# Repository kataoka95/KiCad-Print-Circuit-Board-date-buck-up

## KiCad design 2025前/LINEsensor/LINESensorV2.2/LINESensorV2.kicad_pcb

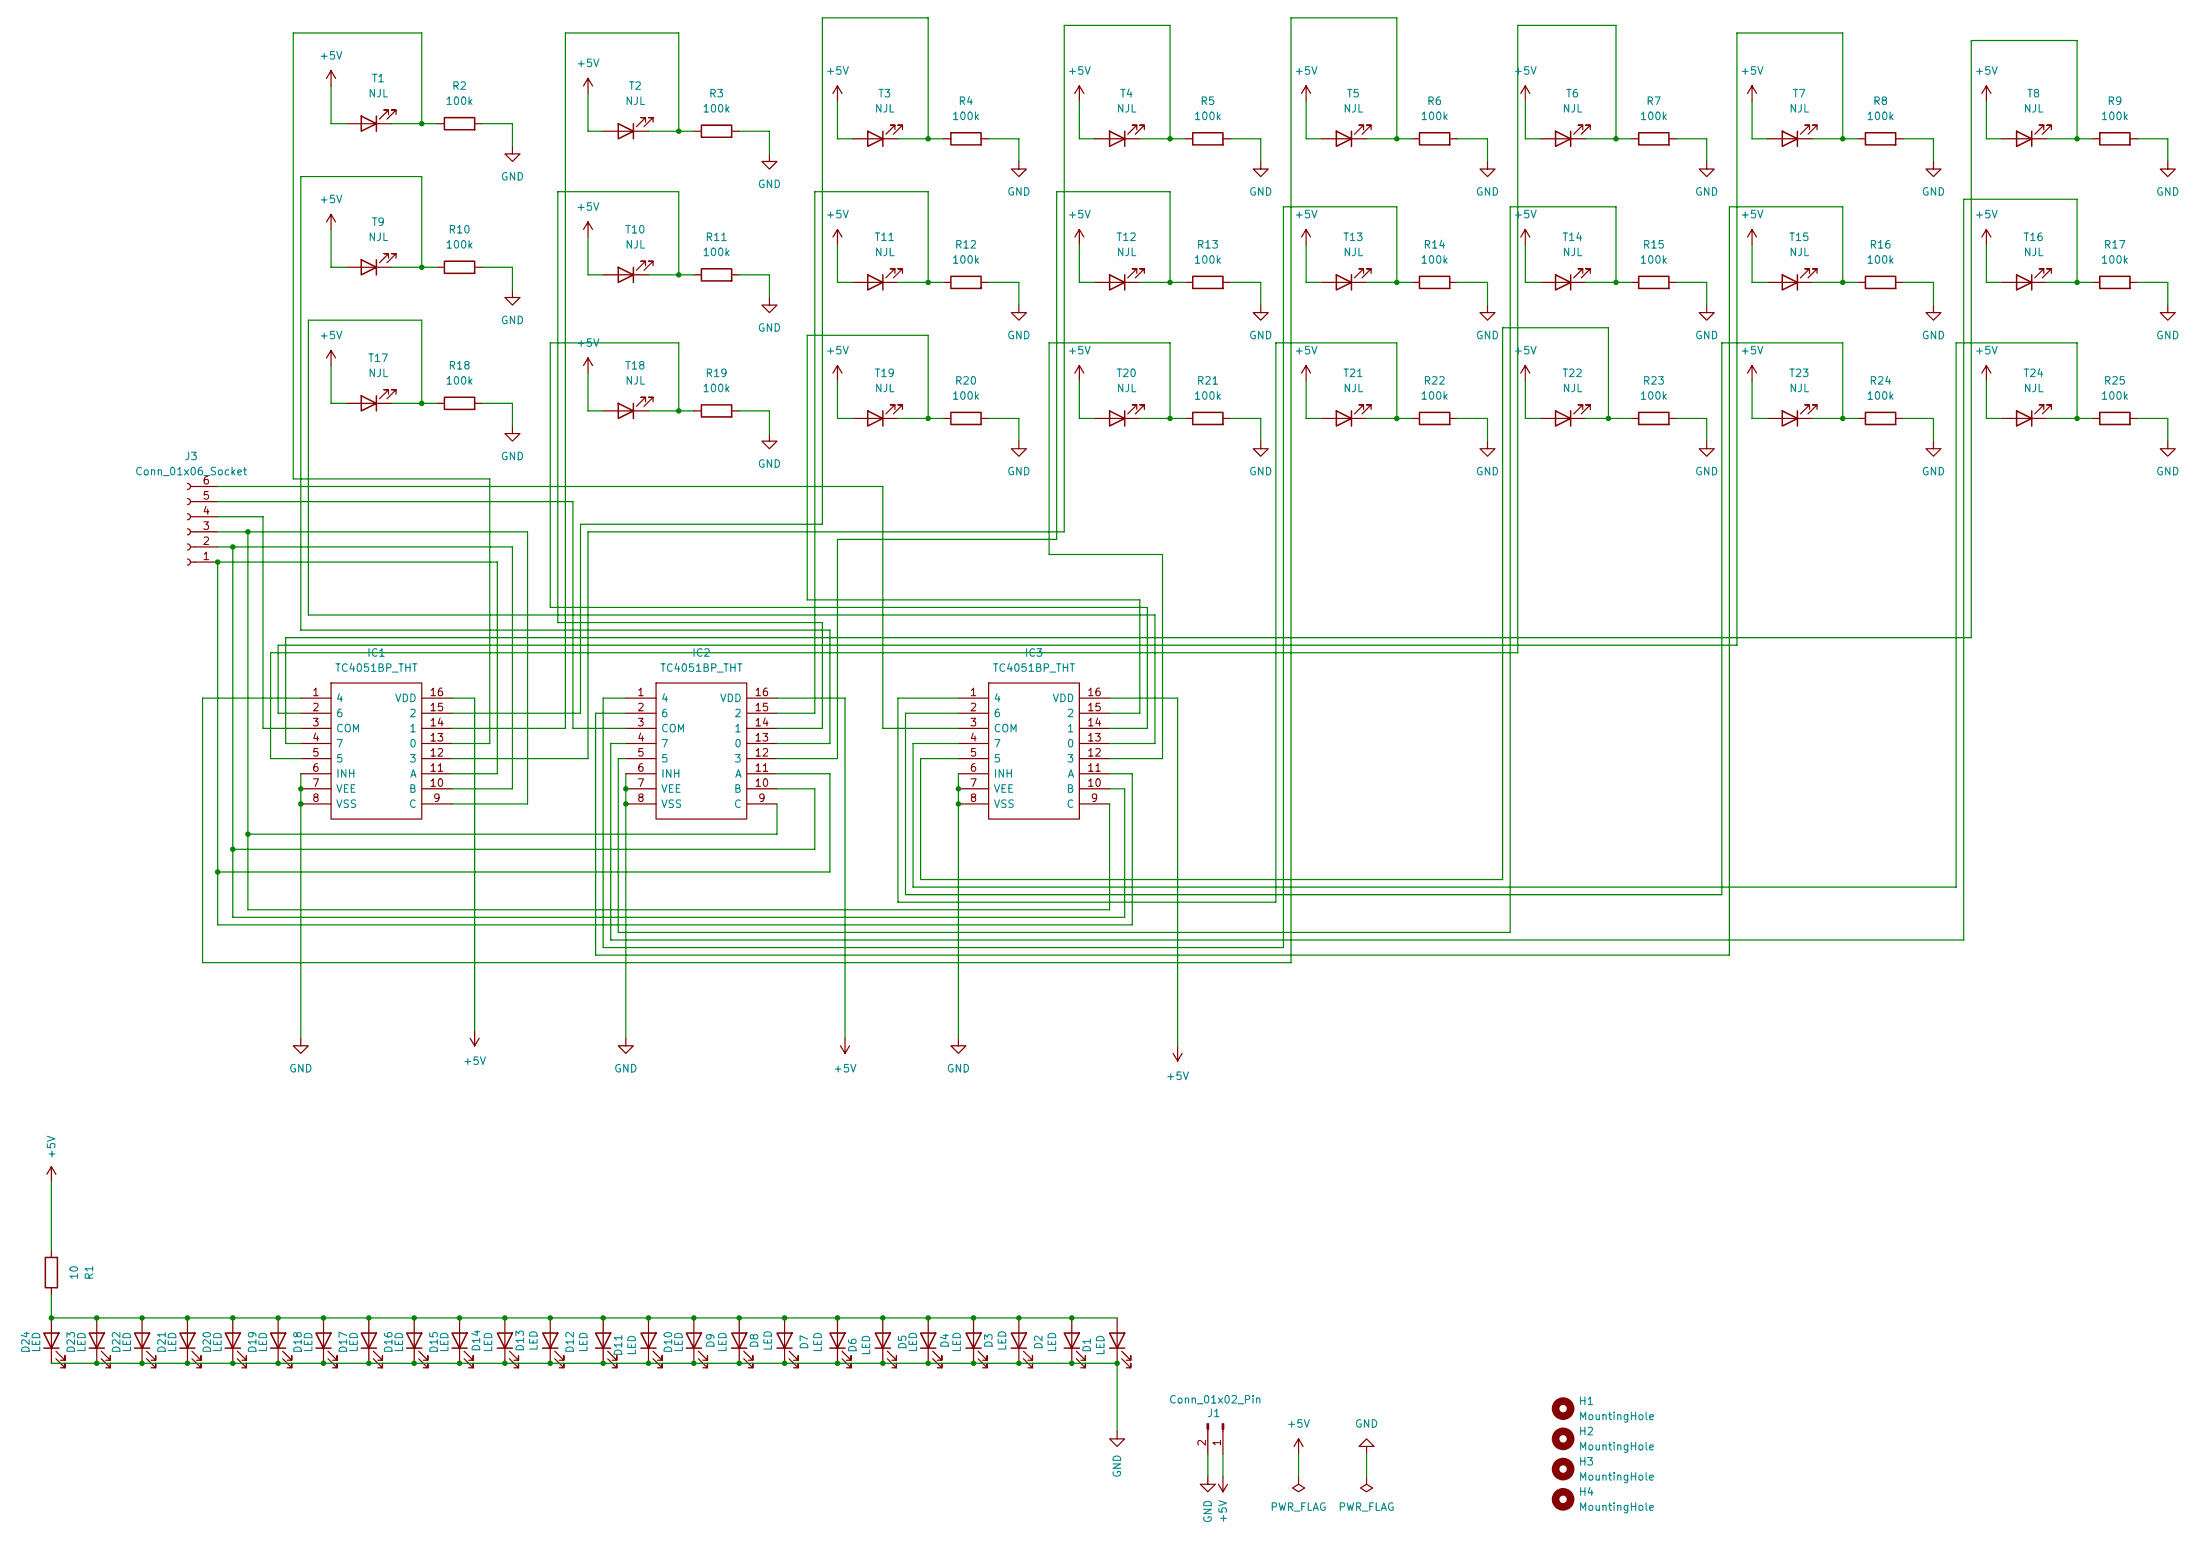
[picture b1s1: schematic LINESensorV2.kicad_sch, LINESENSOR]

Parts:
D1, D2, D3, D4, D5, D6, D7, D8, D9, D10, D11, D12, D13, D14, D15, D16, D17, D18, D19, D20, D21, D22, D23, D24: LED; LED_D5.0mm
H1, H2, H3, H4: MountingHole; MountingHole_3.2mm_M3
IC1, IC2, IC3: TC4051BP_THT; Manufacturer_Part_Number TC4051BP(N,F)
J1: Conn_01x02_Pin; JST_XH_B2B-XH-A_1x02_P2.50mm_Vertical
J3: Conn_01x06_Socket; JST_XH_B6B-XH-A_1x06_P2.50mm_Vertical
R1: 10; R_Axial_DIN0207_L6.3mm_D2.5mm_P10.16mm_Horizontal
R2, R3, R4, R5, R6, R7, R8, R9, R10, R11, R12, R13, R14, R15, R16, R17, R18, R19, R20, R21, R22, R23, R24, R25: 100k; R_Axial_DIN0207_L6.3mm_D2.5mm_P10.16mm_Horizontal
T1, T2, T3, T4, T5, T6, T7, T8, T9, T10, T11, T12, T13, T14, T15, T16, T17, T18, T19, T20, T21, T22, T23, T24: NJL; LED_D5.0mm

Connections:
+5V: IC1.16 (VDD), IC2.16 (VDD), IC3.16 (VDD), J1.1, R1.2, T1.2 (A), T2.2 (A), T3.2 (A), T4.2 (A), T5.2 (A), T6.2 (A), T7.2 (A), T8.2 (A), T9.2 (A), T10.2 (A), T11.2 (A), T12.2 (A), T13.2 (A), T14.2 (A), T15.2 (A), T16.2 (A), T17.2 (A), T18.2 (A), T19.2 (A), T20.2 (A), T21.2 (A), T22.2 (A), T23.2 (A), T24.2 (A)
GND: D1.1 (K), D2.1 (K), D3.1 (K), D4.1 (K), D5.1 (K), D6.1 (K), D7.1 (K), D8.1 (K), D9.1 (K), D10.1 (K), D11.1 (K), D12.1 (K), D13.1 (K), D14.1 (K), D15.1 (K), D16.1 (K), D17.1 (K), D18.1 (K), D19.1 (K), D20.1 (K), D21.1 (K), D22.1 (K), D23.1 (K), D24.1 (K), IC1.6 (INH), IC1.7 (VEE), IC1.8 (VSS), IC2.6 (INH), IC2.7 (VEE), IC2.8 (VSS), IC3.6 (INH), IC3.7 (VEE), IC3.8 (VSS), J1.2, R2.2, R3.2, R4.2, R5.2, R6.2, R7.2, R8.2, R9.2, R10.2, R11.2, R12.2, R13.2, R14.2, R15.2, R16.2, R17.2, R18.2, R19.2, R20.2, R21.2, R22.2, R23.2, R24.2, R25.2
unnamed: D1.2 (A), D2.2 (A), D3.2 (A), D4.2 (A), D5.2 (A), D6.2 (A), D7.2 (A), D8.2 (A), D9.2 (A), D10.2 (A), D11.2 (A), D12.2 (A), D13.2 (A), D14.2 (A), D15.2 (A), D16.2 (A), D17.2 (A), D18.2 (A), D19.2 (A), D20.2 (A), D21.2 (A), D22.2 (A), D23.2 (A), D24.2 (A), R1.1
unnamed: IC1.13 (0), R2.1, T1.1 (K)
unnamed: IC1.14 (1), R3.1, T2.1 (K)
unnamed: IC1.15 (2), R4.1, T3.1 (K)
unnamed: IC1.12 (3), R5.1, T4.1 (K)
unnamed: IC1.1 (4), R6.1, T5.1 (K)
unnamed: IC1.2 (6), R8.1, T7.1 (K)
unnamed: IC1.4 (7), R9.1, T8.1 (K)
unnamed: IC1.11 (A), IC2.11 (A), IC3.11 (A), J3.1
unnamed: IC1.10 (B), IC2.10 (B), IC3.10 (B), J3.2
unnamed: IC1.9 (C), IC2.9 (C), IC3.9 (C), J3.3
unnamed: IC1.3 (COM), J3.4
unnamed: IC2.13 (0), R10.1, T9.1 (K)
unnamed: IC2.14 (1), R11.1, T10.1 (K)
unnamed: IC2.15 (2), R12.1, T11.1 (K)
unnamed: IC2.12 (3), R13.1, T12.1 (K)
unnamed: IC2.1 (4), R14.1, T13.1 (K)
unnamed: IC2.2 (6), R16.1, T15.1 (K)
unnamed: IC2.4 (7), R17.1, T16.1 (K)
unnamed: IC2.3 (COM), J3.5
unnamed: IC3.13 (0), R18.1, T17.1 (K)
unnamed: IC3.14 (1), R19.1, T18.1 (K)
unnamed: IC3.15 (2), R20.1, T19.1 (K)
unnamed: IC3.12 (3), R21.1, T20.1 (K)
unnamed: IC3.1 (4), R22.1, T21.1 (K)
unnamed: IC3.2 (6), R24.1, T23.1 (K)
unnamed: IC3.4 (7), R25.1, T24.1 (K)
unnamed: IC3.3 (COM), J3.6
unnamed: IC1.5, R7.1, T6.1 (K)
unnamed: IC2.5, R15.1, T14.1 (K)
unnamed: IC3.5, R23.1, T22.1 (K)

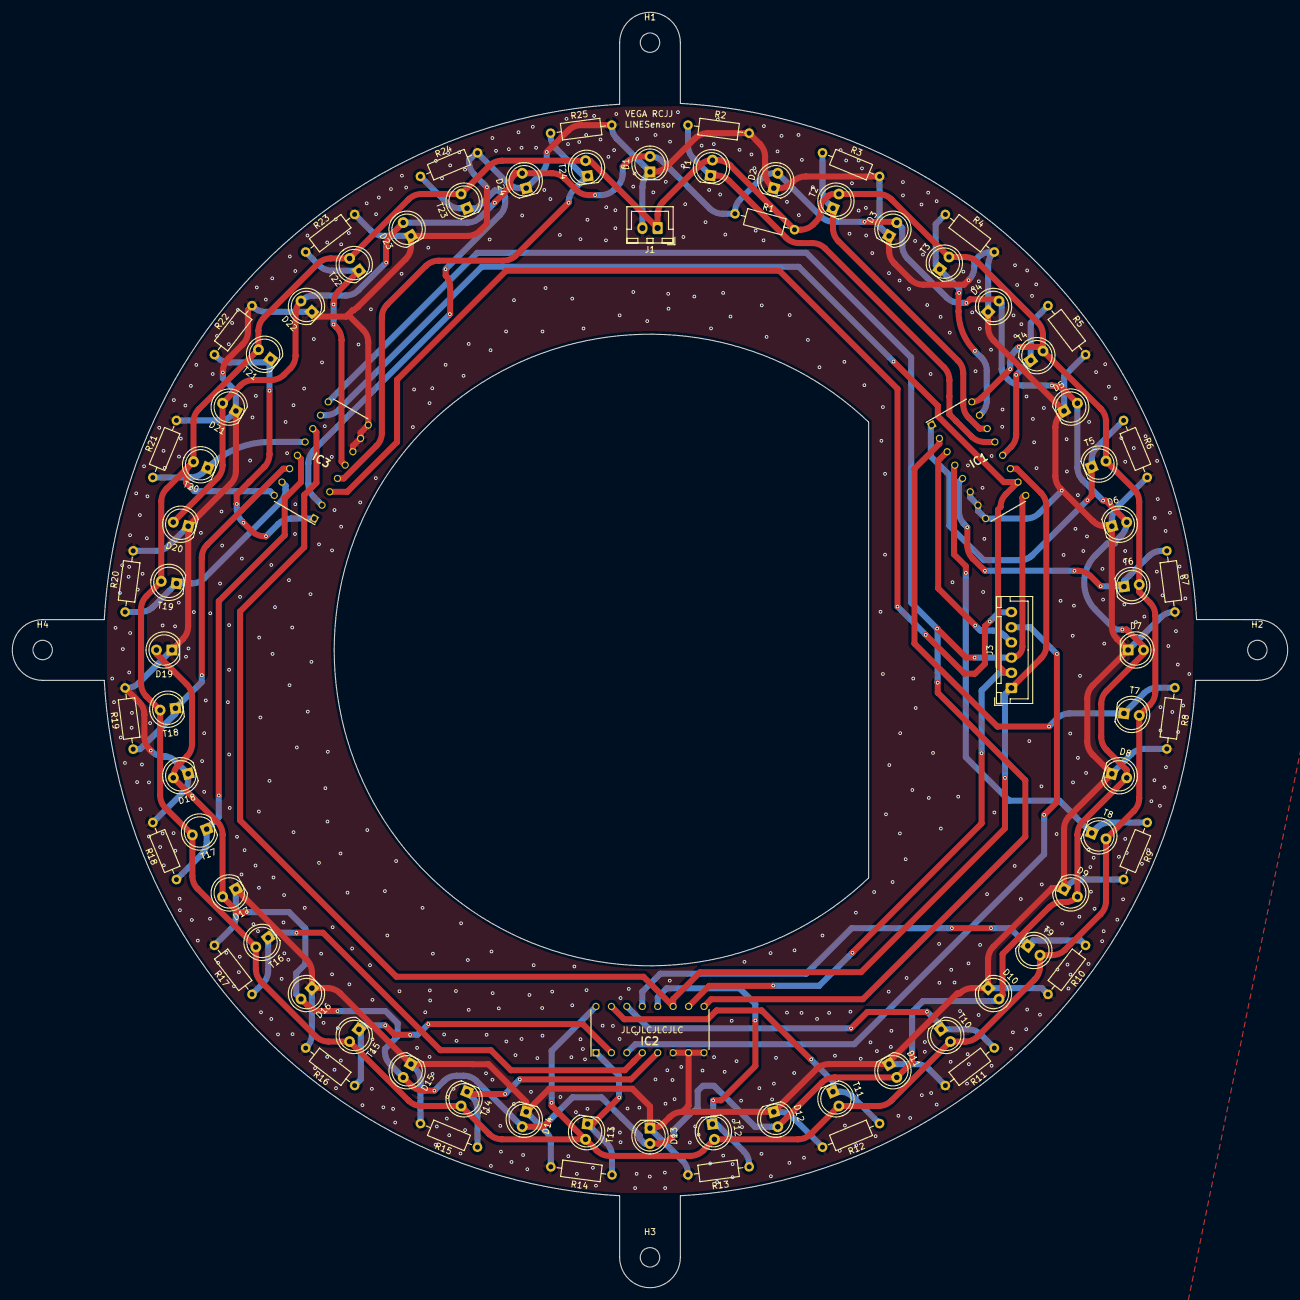
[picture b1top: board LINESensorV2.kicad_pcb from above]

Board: 2 copper layers, 210.0 x 210.0 mm, 82 parts (0 on the bottom side), 33 nets.

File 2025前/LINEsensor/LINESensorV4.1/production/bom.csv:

Designator,Footprint,Quantity,Value,LCSC Part #
"D1, D10, D11, D12, D13, D14, D15, D16, D17, D18, D19, D2, D20, D21, D22, D23, D24, D3, D4, D5, D6, D7, D8, D9",LED Hi-FIELD,24,LED,
"IC1, IC2, IC3",TC4051BP_THT,3,TC4051BP_THT,
J1,CON_522710679_MOL,1,Conn_01x06_Socket,
J2,JST_XH_B2B-XH-A_1x02_P2.50mm_Vertical,1,Conn_01x02_Pin,
R1,R_Axial_DIN0207_L6.3mm_D2.5mm_P10.16mm_Horizontal,1,10,
"R10, R11, R12, R13, R14, R15, R16, R17, R18, R19, R2, R20, R21, R22, R23, R24, R25, R3, R4, R5, R6, R7, R8, R9",0603,24,100k,
"T1, T10, T11, T12, T13, T14, T15, T16, T17, T18, T19, T2, T20, T21, T22, T23, T24, T3, T4, T5, T6, T7, T8, T9",NJL7052L,24,NJL,

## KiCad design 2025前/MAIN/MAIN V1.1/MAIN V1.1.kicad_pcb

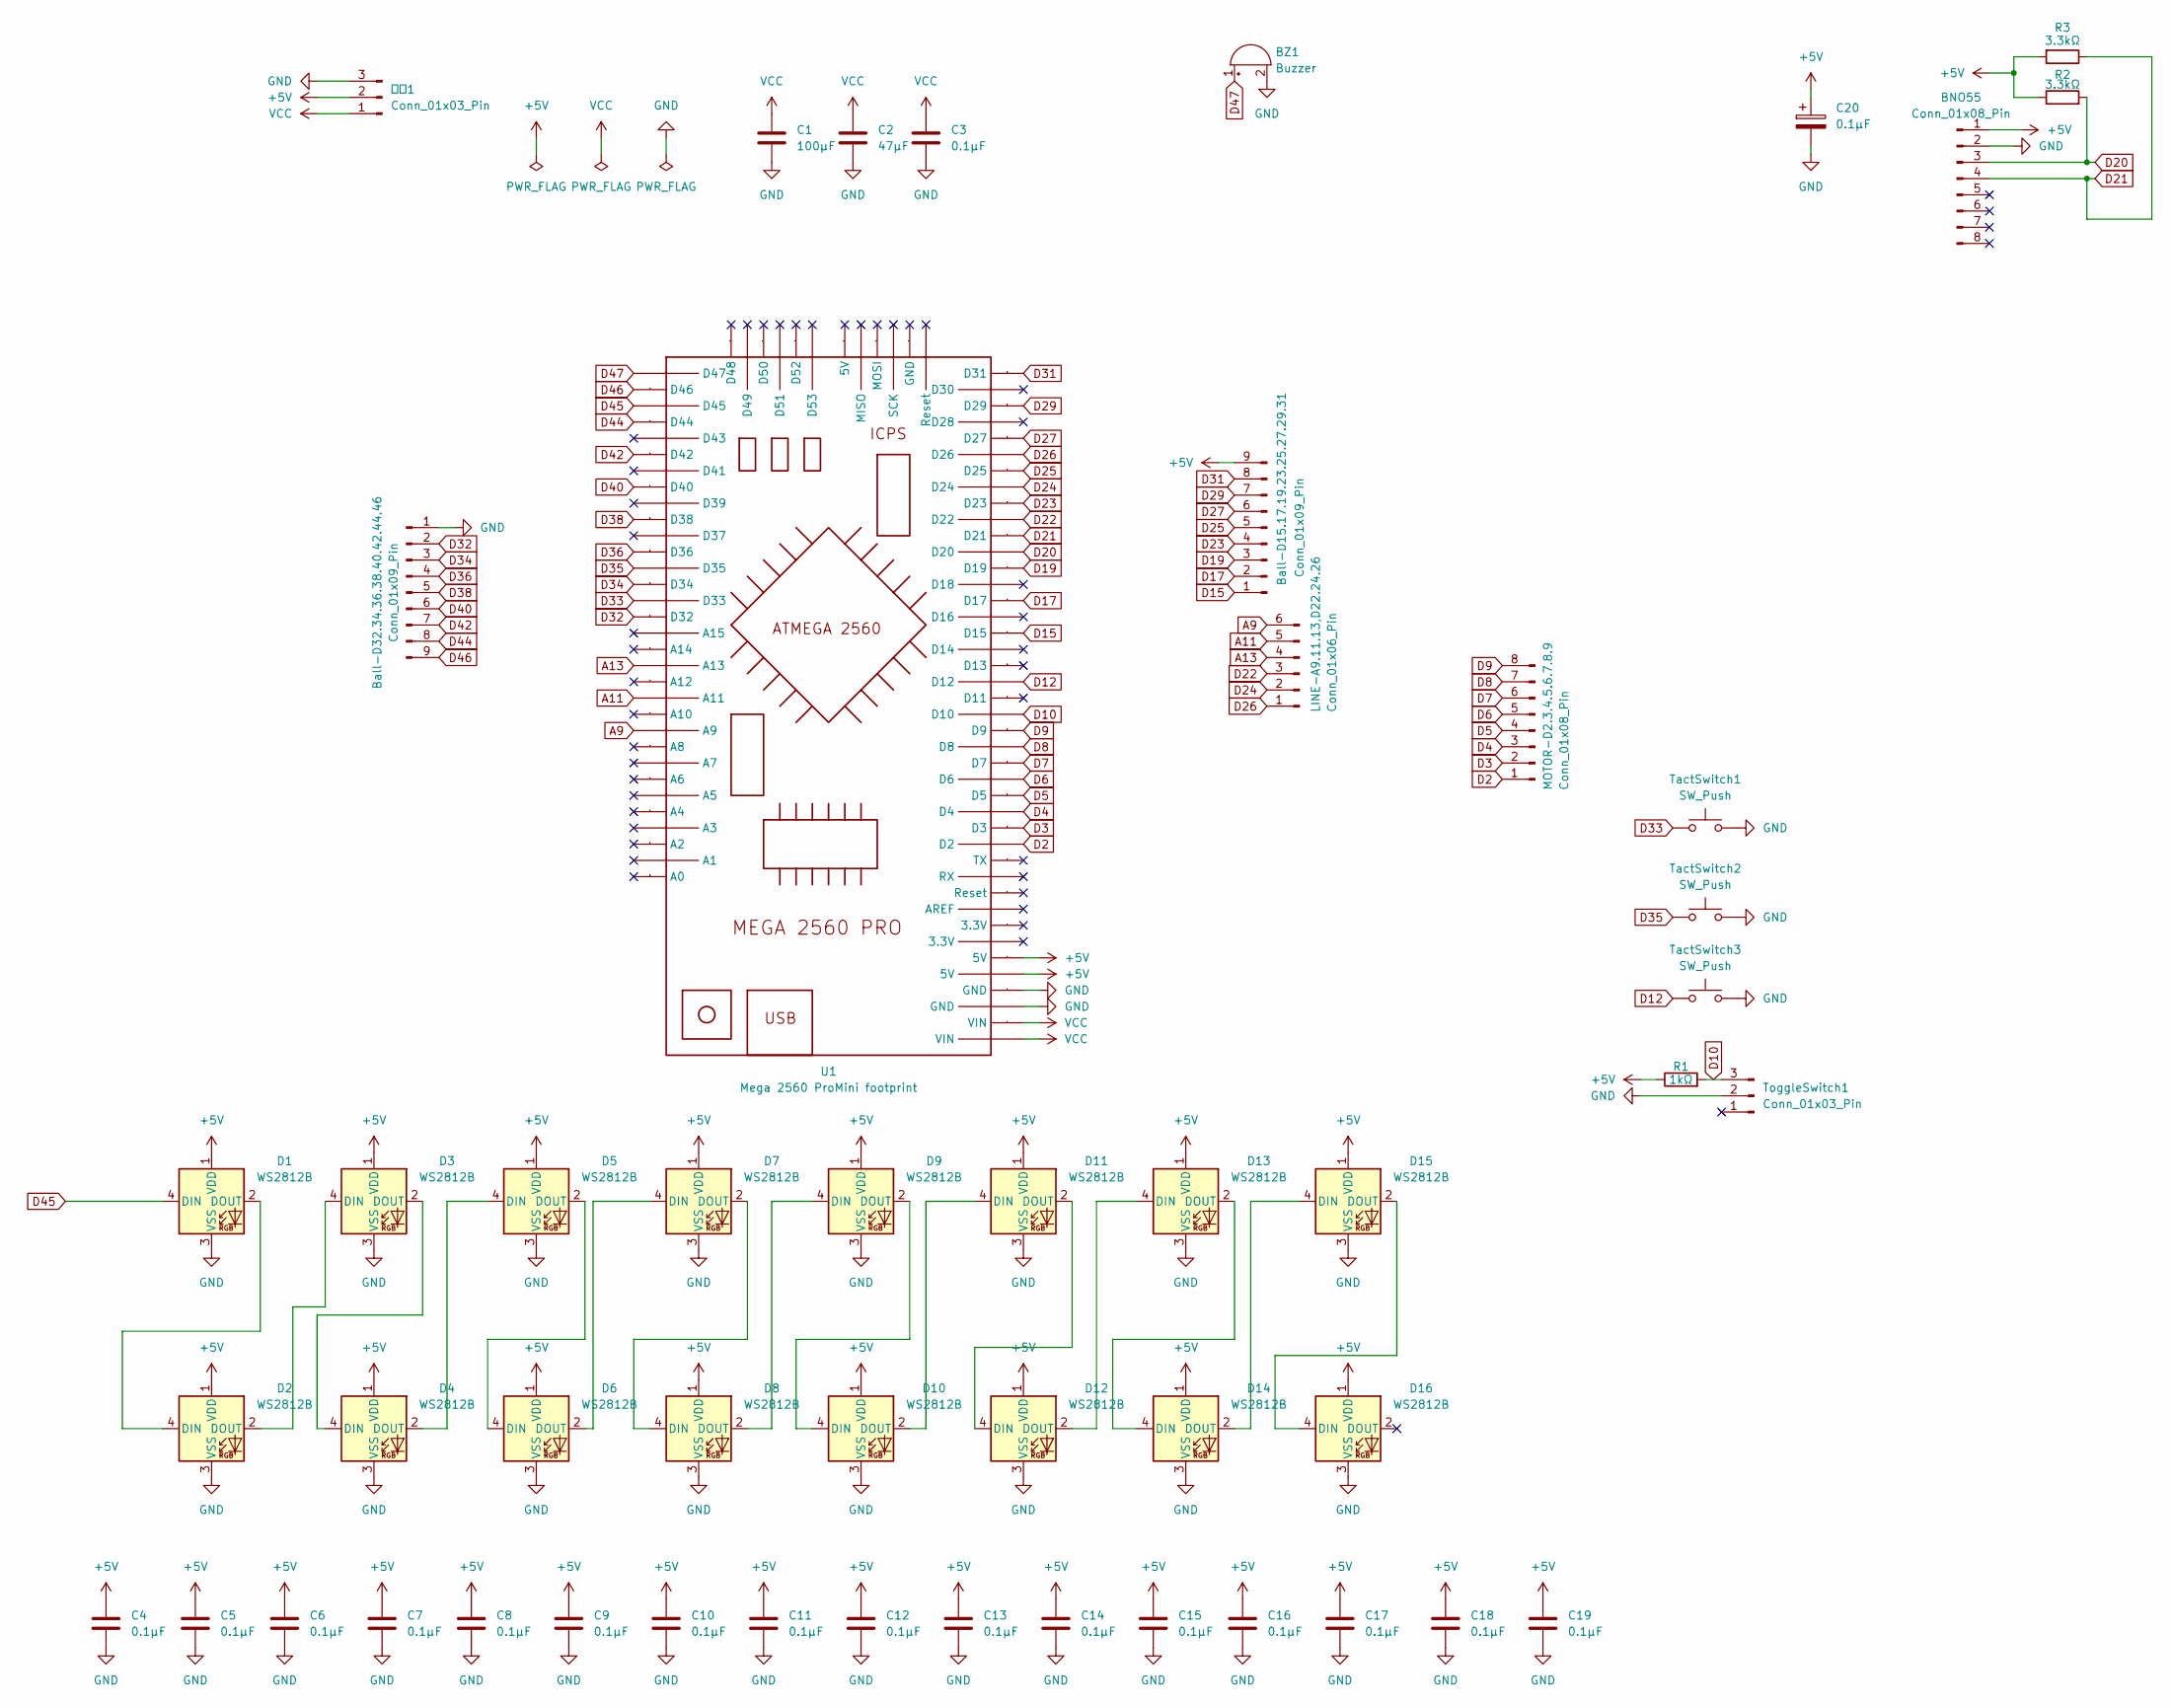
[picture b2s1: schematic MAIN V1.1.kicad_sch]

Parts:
BNO55: Conn_01x08_Pin; BNO055
BZ1: Buzzer; Buzzer UDX01CLFPH
Ball-D15.17.19.23.25.27.29.31, Ball-D32.34.36.38.40.42.44.46: Conn_01x09_Pin; PinSocket_1x09_P2.54mm_Vertical
C1: 100μF; CP_Radial_D5.0mm_P2.50mm
C2: 47μF; CP_Radial_D5.0mm_P2.50mm
C3: 0.1μF; CP_Radial_D5.0mm_P2.50mm
C4, C5, C6, C7, C8, C9, C10, C11, C12, C13, C14, C15, C16, C17, C18, C19, C20: 0.1μF; C_0603_1608Metric_Pad1.08x0.95mm_HandSolder
D1, D2, D3, D4, D5, D6, D7, D8, D9, D10, D11, D12, D13, D14, D15, D16: WS2812B; LED_WS2812B_PLCC4_5.0x5.0mm_P3.2mm
LINE-A9.11.13,D22.24.26: Conn_01x06_Pin; CON_522710679_MOL
MOTOR-D2.3.4.5.6.7.8.9: Conn_01x08_Pin; CON_522710879_MOL
R1: 1kΩ; R_0805_2012Metric_Pad1.20x1.40mm_HandSolder
R2, R3: 3.3kΩ; R_0805_2012Metric_Pad1.20x1.40mm_HandSolder
TactSwitch1, TactSwitch3: SW_Push; SW_PUSH_6mm
TactSwitch2: SW_Push; SW_TL1100EF160Q
ToggleSwitch1: Conn_01x03_Pin; PinSocket_1x03_P2.54mm_Vertical
U1: Mega 2560 ProMini footprint; ARDUINO_MEGA_2560_PRO; Manufacturer Part Arduino Mega 2560 Pro Mini
電源1: Conn_01x03_Pin; JST_XH_B3B-XH-A_1x03_P2.50mm_Vertical

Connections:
+5V: BNO55.1, Ball-D15.17.19.23.25.27.29.31.9, C4.1, C5.1, C6.1, C7.1, C8.1, C9.1, C10.1, C11.1, C12.1, C13.1, C14.1, C15.1, C16.1, C17.1, C18.1, C19.1, C20.1, D1.1 (VDD), D2.1 (VDD), D3.1 (VDD), D4.1 (VDD), D5.1 (VDD), D6.1 (VDD), D7.1 (VDD), D8.1 (VDD), D9.1 (VDD), D10.1 (VDD), D11.1 (VDD), D12.1 (VDD), D13.1 (VDD), D14.1 (VDD), D15.1 (VDD), D16.1 (VDD), R1.1, R2.1, R3.2, U1.5 (5V), U1.6 (5V), 電源1.2; also elsewhere on the board
A9: LINE-A9.11.13,D22.24.26.6, U1.52 (A9)
A11: LINE-A9.11.13,D22.24.26.5, U1.54 (A11)
A13: LINE-A9.11.13,D22.24.26.4, U1.56 (A13)
D2: MOTOR-D2.3.4.5.6.7.8.9.1, U1.13 (D2)
D3: MOTOR-D2.3.4.5.6.7.8.9.2, U1.14 (D3)
D4: MOTOR-D2.3.4.5.6.7.8.9.3, U1.15 (D4)
D5: MOTOR-D2.3.4.5.6.7.8.9.4, U1.16 (D5)
D6: MOTOR-D2.3.4.5.6.7.8.9.5, U1.17 (D6)
D7: MOTOR-D2.3.4.5.6.7.8.9.6, U1.18 (D7)
D8: MOTOR-D2.3.4.5.6.7.8.9.7, U1.19 (D8)
D9: MOTOR-D2.3.4.5.6.7.8.9.8, U1.20 (D9)
D10: R1.2, ToggleSwitch1.3, U1.21 (D10)
D12: TactSwitch3.1, U1.23 (D12)
D15: Ball-D15.17.19.23.25.27.29.31.1, U1.26 (D15)
D17: Ball-D15.17.19.23.25.27.29.31.2, U1.28 (D17)
D19: Ball-D15.17.19.23.25.27.29.31.3, U1.30 (D19)
D20: BNO55.3, R2.2, U1.31 (D20)
D21: BNO55.4, R3.1, U1.32 (D21)
D22: LINE-A9.11.13,D22.24.26.3, U1.33 (D22)
D23: Ball-D15.17.19.23.25.27.29.31.4, U1.34 (D23)
D24: LINE-A9.11.13,D22.24.26.2, U1.35 (D24)
D25: Ball-D15.17.19.23.25.27.29.31.5, U1.36 (D25)
D26: LINE-A9.11.13,D22.24.26.1, U1.37 (D26)
D27: Ball-D15.17.19.23.25.27.29.31.6, U1.38 (D27)
D29: Ball-D15.17.19.23.25.27.29.31.7, U1.40 (D29)
D31: Ball-D15.17.19.23.25.27.29.31.8, U1.42 (D31)
D32: Ball-D32.34.36.38.40.42.44.46.2, U1.59 (D32)
D33: TactSwitch1.1, U1.60 (D33)
D34: Ball-D32.34.36.38.40.42.44.46.3, U1.61 (D34)
D35: TactSwitch2.1, U1.62 (D35)
D36: Ball-D32.34.36.38.40.42.44.46.4, U1.63 (D36)
D38: Ball-D32.34.36.38.40.42.44.46.5, U1.65 (D38)
D40: Ball-D32.34.36.38.40.42.44.46.6, U1.67 (D40)
D42: Ball-D32.34.36.38.40.42.44.46.7, U1.69 (D42)
D44: Ball-D32.34.36.38.40.42.44.46.8, U1.71 (D44)
D45: D1.4 (DIN), U1.72 (D45)
D46: Ball-D32.34.36.38.40.42.44.46.9, U1.73 (D46)
D47: BZ1.1 (+), U1.74 (D47)
GND: BNO55.2, BZ1.2 (-), Ball-D32.34.36.38.40.42.44.46.1, C1.2, C2.2, C3.2, C4.2, C5.2, C6.2, C7.2, C8.2, C9.2, C10.2, C11.2, C12.2, C13.2, C14.2, C15.2, C16.2, C17.2, C18.2, C19.2, C20.2, D1.3 (VSS), D2.3 (VSS), D3.3 (VSS), D4.3 (VSS), D5.3 (VSS), D6.3 (VSS), D7.3 (VSS), D8.3 (VSS), D9.3 (VSS), D10.3 (VSS), D11.3 (VSS), D12.3 (VSS), D13.3 (VSS), D14.3 (VSS), D15.3 (VSS), D16.3 (VSS), TactSwitch1.2, TactSwitch2.2, TactSwitch3.2, ToggleSwitch1.2, U1.3 (GND), U1.4 (GND), 電源1.3; also elsewhere on the board
unnamed: D1.2 (DOUT), D2.4 (DIN)
unnamed: D2.2 (DOUT), D3.4 (DIN)
unnamed: D3.2 (DOUT), D4.4 (DIN)
unnamed: D4.2 (DOUT), D5.4 (DIN)
unnamed: D5.2 (DOUT), D6.4 (DIN)
unnamed: D6.2 (DOUT), D7.4 (DIN)
unnamed: D7.2 (DOUT), D8.4 (DIN)
unnamed: D8.2 (DOUT), D9.4 (DIN)
unnamed: D9.2 (DOUT), D10.4 (DIN)
unnamed: D10.2 (DOUT), D11.4 (DIN)
unnamed: D11.2 (DOUT), D12.4 (DIN)
unnamed: D12.2 (DOUT), D13.4 (DIN)
unnamed: D13.2 (DOUT), D14.4 (DIN)
unnamed: D14.2 (DOUT), D15.4 (DIN)
unnamed: D15.2 (DOUT), D16.4 (DIN)
VCC: C1.1, C2.1, C3.1, U1.1 (VIN), U1.2 (VIN), 電源1.1; also elsewhere on the board

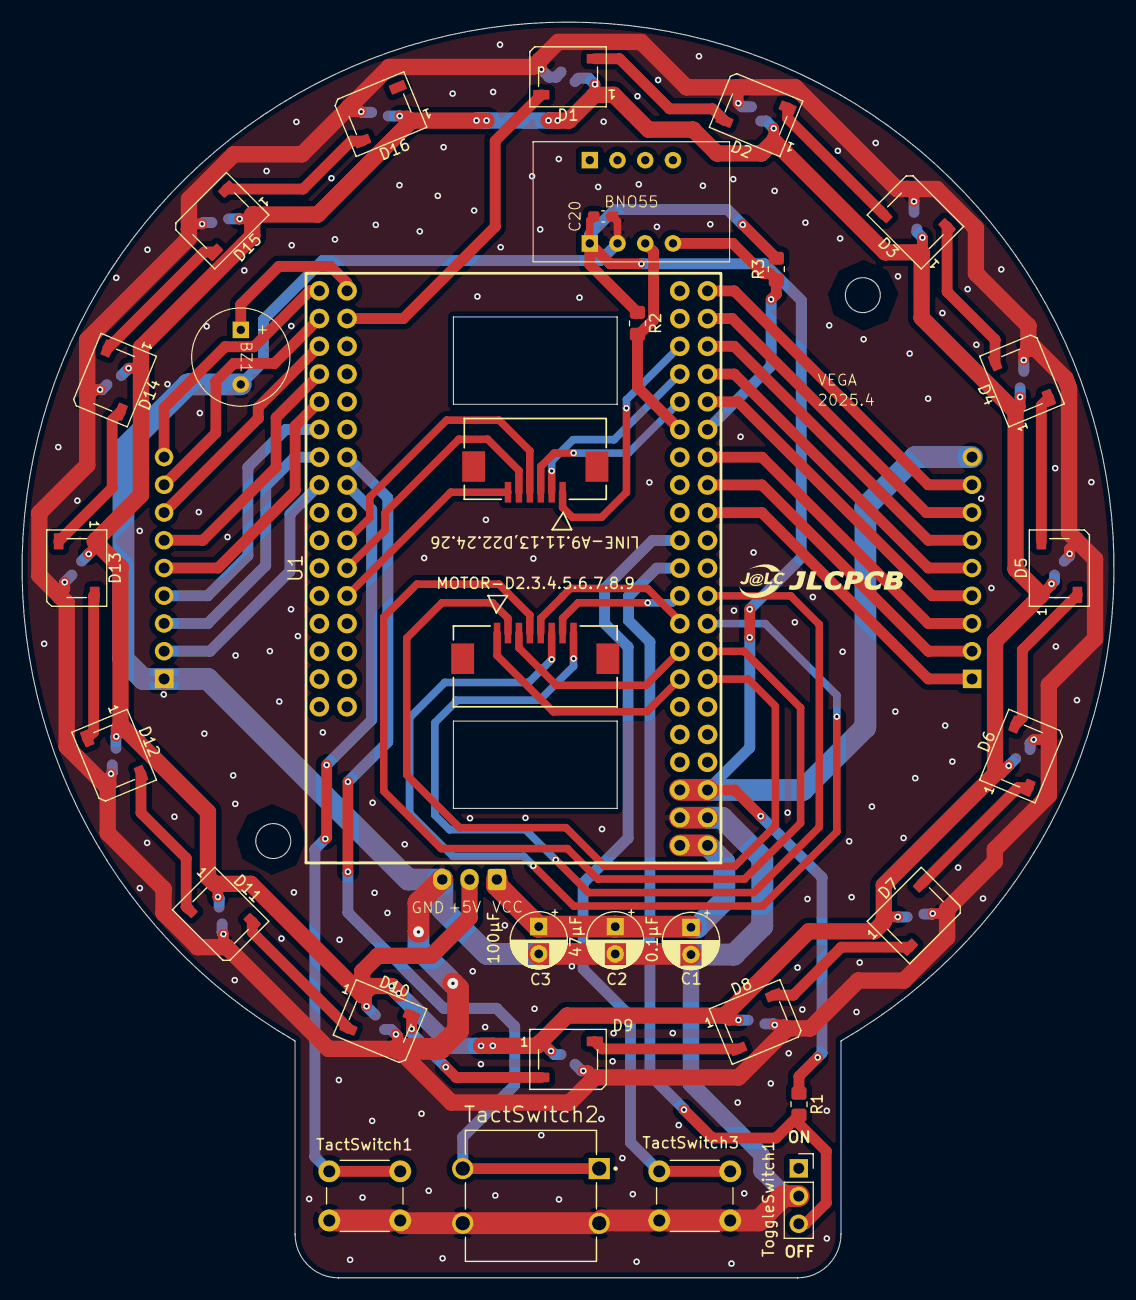
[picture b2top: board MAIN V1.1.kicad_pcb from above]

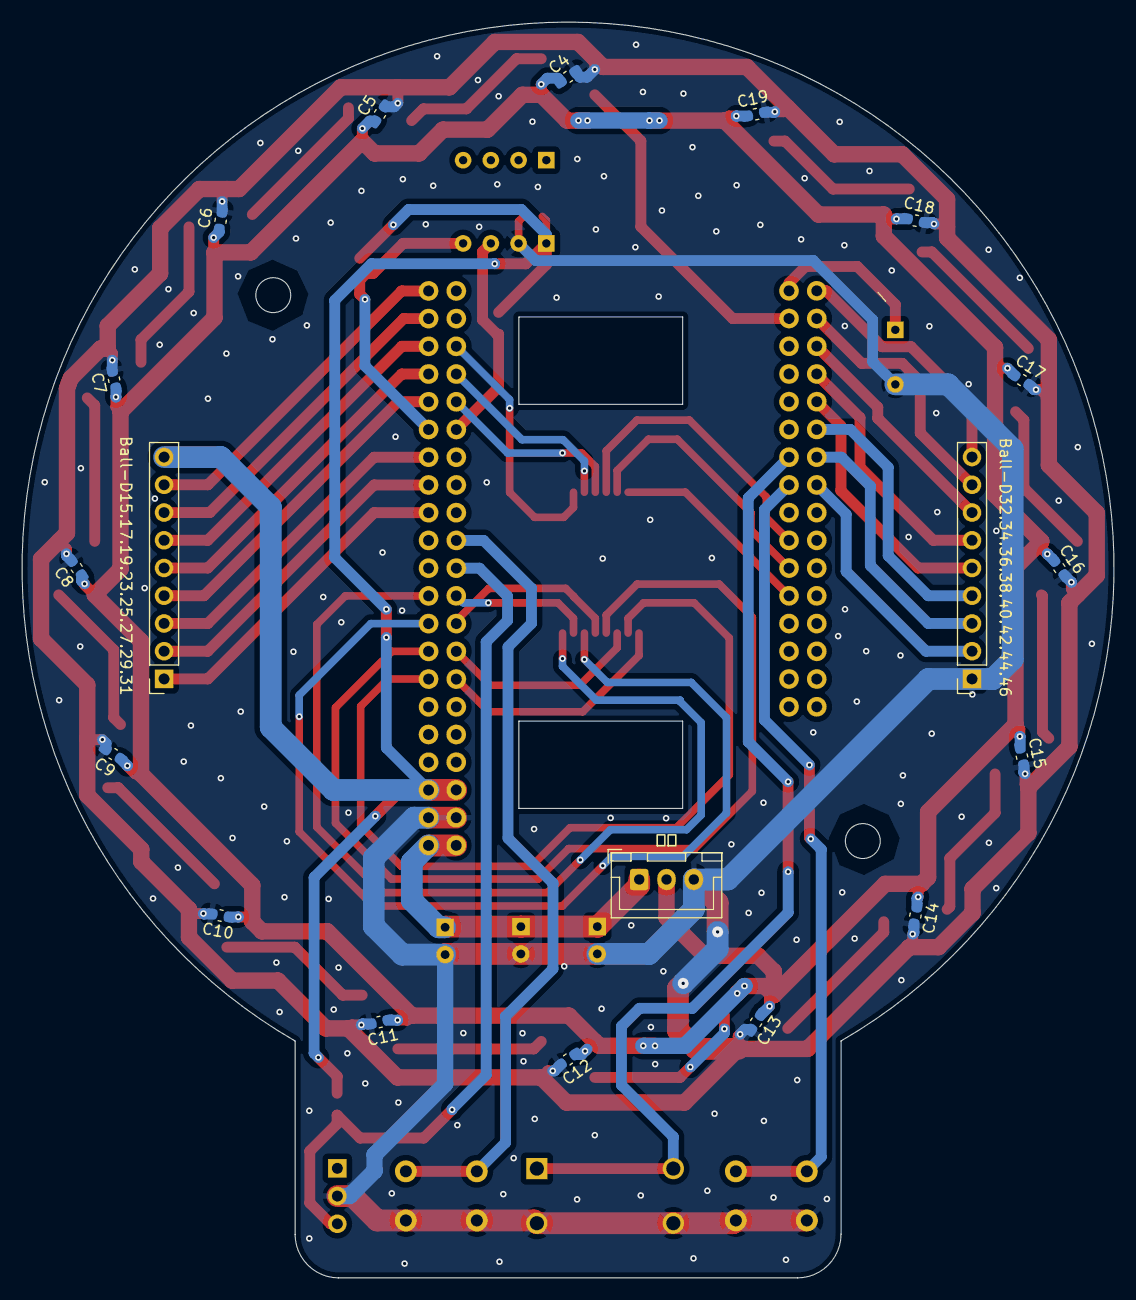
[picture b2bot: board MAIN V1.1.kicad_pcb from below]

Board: 2 copper layers, 100.0 x 115.0 mm, 51 parts (19 on the bottom side), 56 nets.

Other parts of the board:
電源: Conn_01x03_Pin; JST_XH_B3B-XH-A_1x03_P2.50mm_Vertical

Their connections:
+5V: 電源.2; also elsewhere on the board
GND: 電源.3; also elsewhere on the board
VCC: 電源.1; also elsewhere on the board

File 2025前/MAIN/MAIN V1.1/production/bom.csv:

Designator,Footprint,Quantity,Value,LCSC Part #
"BALL-D15.17.19.23.25.27.29.31, BALL-D32.34.36.38.40.42.44.46",PinSocket_1x09_P2.54mm_Vertical,2,Conn_01x09_Pin,
BNO55,BNO055,1,Conn_01x08_Pin,
BZ1,Buzzer UDX01CLFPH,1,Buzzer,
C1,CP_Radial_D5.0mm_P2.50mm,1,100μF,
"C10, C11, C12, C13, C14, C15, C16, C17, C18, C19, C20, C4, C5, C6, C7, C8, C9",0603,17,0.1μF,
C2,CP_Radial_D5.0mm_P2.50mm,1,47μF,
C3,CP_Radial_D5.0mm_P2.50mm,1,0.1μF,
"D1, D10, D11, D12, D13, D14, D15, D16, D2, D3, D4, D5, D6, D7, D8, D9",LED_WS2812B_PLCC4_5.0x5.0mm_P3.2mm,16,WS2812B,
"LINE-A9.11.13,D22.24.26",CON_522710679_MOL,1,Conn_01x06_Pin,
MOTOR-D2.3.4.5.6.7.8.9,CON_522710879_MOL,1,Conn_01x08_Pin,
R1,0805,1,1kΩ,
"R2, R3",0805,2,3.3kΩ,
"TACTSWITCH1, TACTSWITCH3",SW_PUSH_6mm,2,SW_Push,
TACTSWITCH2,SW_TL1100EF160Q,1,SW_Push,
TOGGLESWITCH1,PinSocket_1x03_P2.54mm_Vertical,1,Conn_01x03_Pin,
U1,ARDUINO_MEGA_2560_PRO,1,Mega 2560 ProMini footprint,
電源,JST_XH_B3B-XH-A_1x03_P2.50mm_Vertical,1,Conn_01x03_Pin,

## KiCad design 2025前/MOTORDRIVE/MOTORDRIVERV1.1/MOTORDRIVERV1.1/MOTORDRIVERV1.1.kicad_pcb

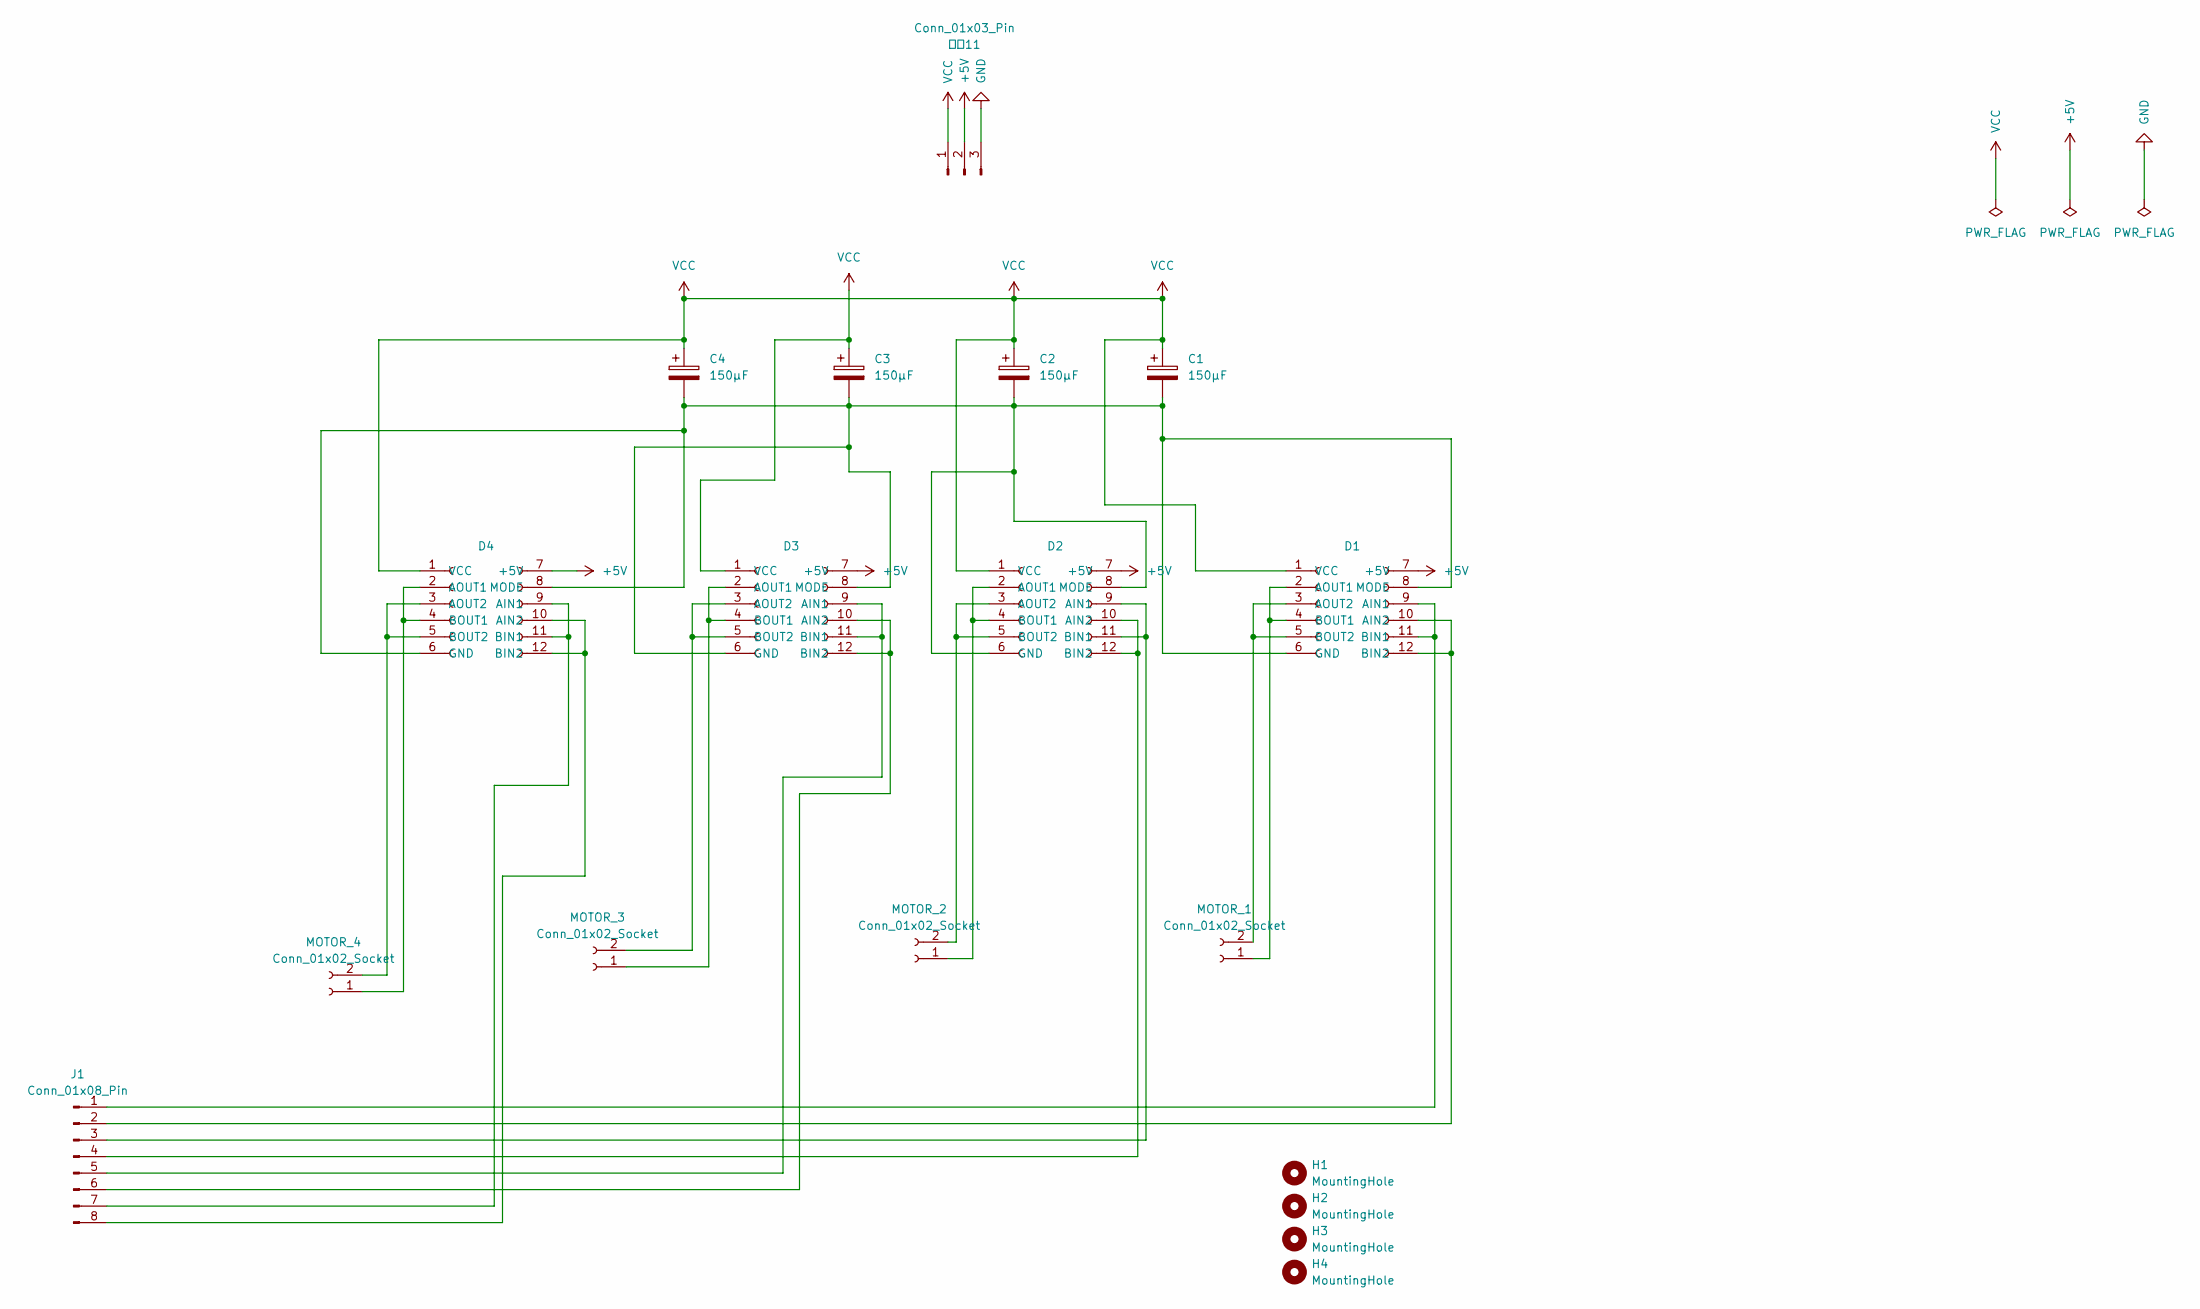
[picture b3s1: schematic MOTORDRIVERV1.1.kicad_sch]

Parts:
C1, C2, C3, C4: 150μF; CP_Radial_D5.0mm_P2.00mm
D1, D2, D3, D4: DRV8835
H1, H2, H3, H4: MountingHole; MountingHole_3.2mm_M3
J1: Conn_01x08_Pin; JST_XH_B8B-XH-A_1x08_P2.50mm_Vertical
MOTOR_1, MOTOR_2, MOTOR_3, MOTOR_4: Conn_01x02_Socket; JST_XH_B2B-XH-A_1x02_P2.50mm_Vertical
電源11: Conn_01x03_Pin; PinSocket_1x03_P2.54mm_Vertical

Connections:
+5V: D1.7 (+5V), D2.7 (+5V), D3.7 (+5V), D4.7 (+5V), 電源11.2; also elsewhere on the board
unnamed: D1.9 (AIN1), D1.11 (BIN1), J1.1
unnamed: D1.10 (AIN2), D1.12 (BIN2), J1.2
unnamed: D1.2 (AOUT1), D1.4 (BOUT1), MOTOR_1.1
unnamed: D1.3 (AOUT2), D1.5 (BOUT2), MOTOR_1.2
unnamed: C1.2, C2.2, C3.2, C4.2, D1.6 (GND), D1.8 (MODE), D2.6 (GND), D2.8 (MODE), D3.6 (GND), D3.8 (MODE), D4.6 (GND), D4.8 (MODE)
unnamed: D2.9 (AIN1), D2.11 (BIN1), J1.3
unnamed: D2.10 (AIN2), D2.12 (BIN2), J1.4
unnamed: D2.2 (AOUT1), D2.4 (BOUT1), MOTOR_2.1
unnamed: D2.3 (AOUT2), D2.5 (BOUT2), MOTOR_2.2
unnamed: D3.9 (AIN1), D3.11 (BIN1), J1.5
unnamed: D3.10 (AIN2), D3.12 (BIN2), J1.6
unnamed: D3.2 (AOUT1), D3.4 (BOUT1), MOTOR_3.1
unnamed: D3.3 (AOUT2), D3.5 (BOUT2), MOTOR_3.2
unnamed: D4.9 (AIN1), D4.11 (BIN1), J1.7
unnamed: D4.10 (AIN2), D4.12 (BIN2), J1.8
unnamed: D4.2 (AOUT1), D4.4 (BOUT1), MOTOR_4.1
unnamed: D4.3 (AOUT2), D4.5 (BOUT2), MOTOR_4.2
VCC: C1.1, C2.1, C3.1, C4.1, D1.1 (VCC), D2.1 (VCC), D3.1 (VCC), D4.1 (VCC), 電源11.1; also elsewhere on the board

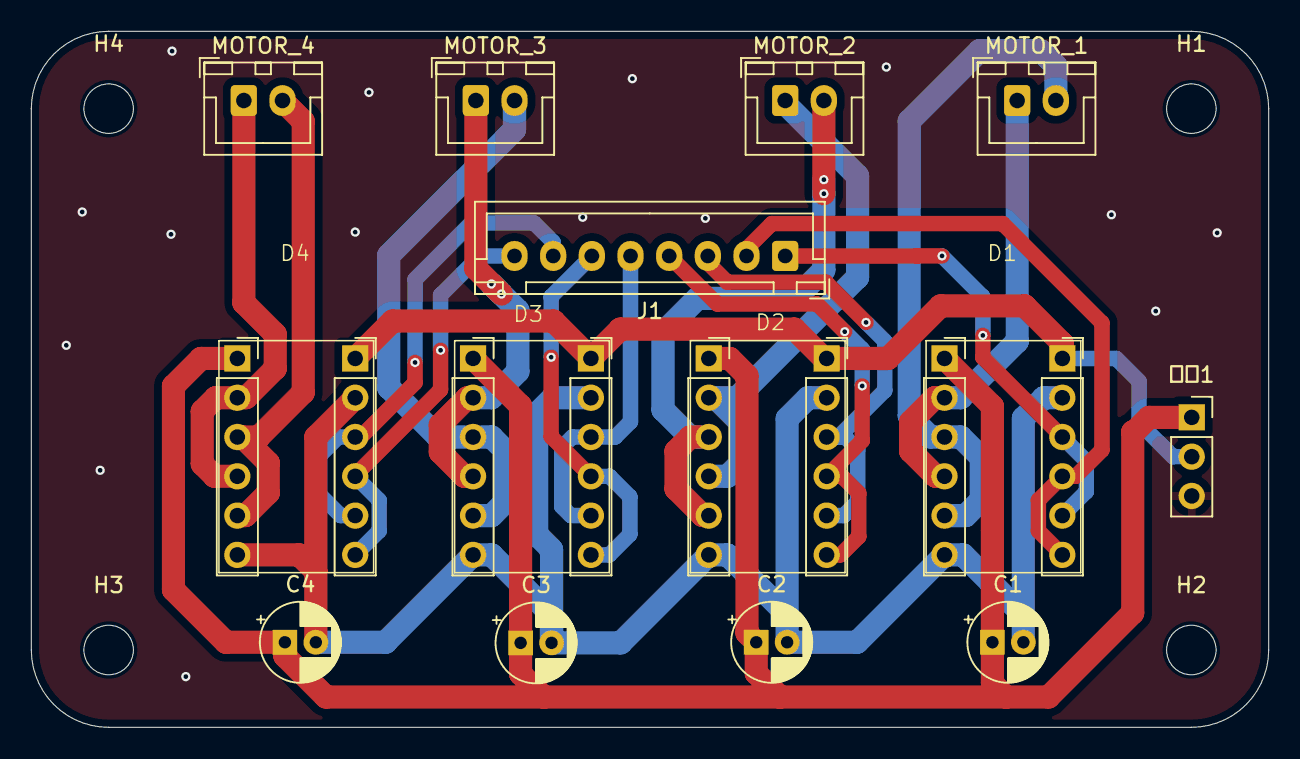
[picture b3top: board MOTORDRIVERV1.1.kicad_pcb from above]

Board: 2 copper layers, 80.0 x 45.0 mm, 18 parts (0 on the bottom side), 19 nets.

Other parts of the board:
電源1: Conn_01x03_Pin; PinSocket_1x03_P2.54mm_Vertical

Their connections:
+5V: 電源1.2; also elsewhere on the board
VCC: 電源1.1; also elsewhere on the board
